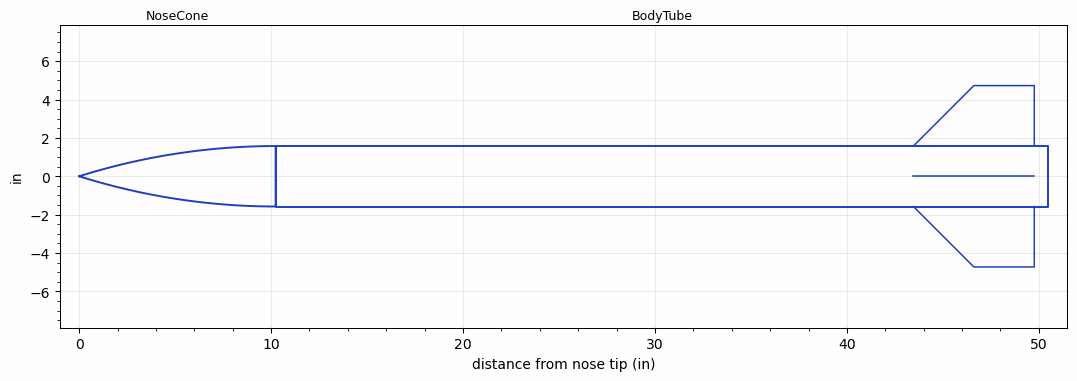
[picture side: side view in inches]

<RASAeroDocument>
 <FileVersion>2</FileVersion>
 <RocketDesign>
  <NoseCone>
   <Length>10.2362</Length>
   <Diameter>3.1496</Diameter>
   <Shape>Tangent Ogive</Shape>
   <Location>0</Location>
  </NoseCone>
  <BodyTube>
   <Length>40.2362</Length>
   <Diameter>3.1496</Diameter>
   <Location>10.2362</Location>
   <Fin>
    <Count>4</Count>
    <Chord>6.2992</Chord>
    <Span>3.1496</Span>
    <SweepDistance>3.1496</SweepDistance>
    <TipChord>3.1496</TipChord>
    <Thickness>0.1181</Thickness>
    <Location>7.0079</Location>
    <AirfoilSection>Square</AirfoilSection>
   </Fin>
  </BodyTube>
  <Surface>Smooth (Zero Roughness)</Surface>
  <ModifiedBarrowman>False</ModifiedBarrowman>
  <Turbulence>False</Turbulence>
  <UseBooster1>False</UseBooster1>
  <UseBooster2>False</UseBooster2>
 </RocketDesign>
 <LaunchSite>
  <Altitude>0</Altitude>
  <Pressure>0</Pressure>
  <RodAngle>0</RodAngle>
  <RodLength>4</RodLength>
  <Temperature>74</Temperature>
  <WindSpeed>0</WindSpeed>
 </LaunchSite>
 <Recovery>
  <Altitude1>1000</Altitude1>
  <Altitude2>1000</Altitude2>
  <DeviceType1>None</DeviceType1>
  <DeviceType2>None</DeviceType2>
  <Event1>False</Event1>
  <Event2>False</Event2>
  <Size1>1</Size1>
  <Size2>1</Size2>
  <EventType1>None</EventType1>
  <EventType2>None</EventType2>
  <CD1>1.33</CD1>
  <CD2>1.33</CD2>
 </Recovery>
</RASAeroDocument>
